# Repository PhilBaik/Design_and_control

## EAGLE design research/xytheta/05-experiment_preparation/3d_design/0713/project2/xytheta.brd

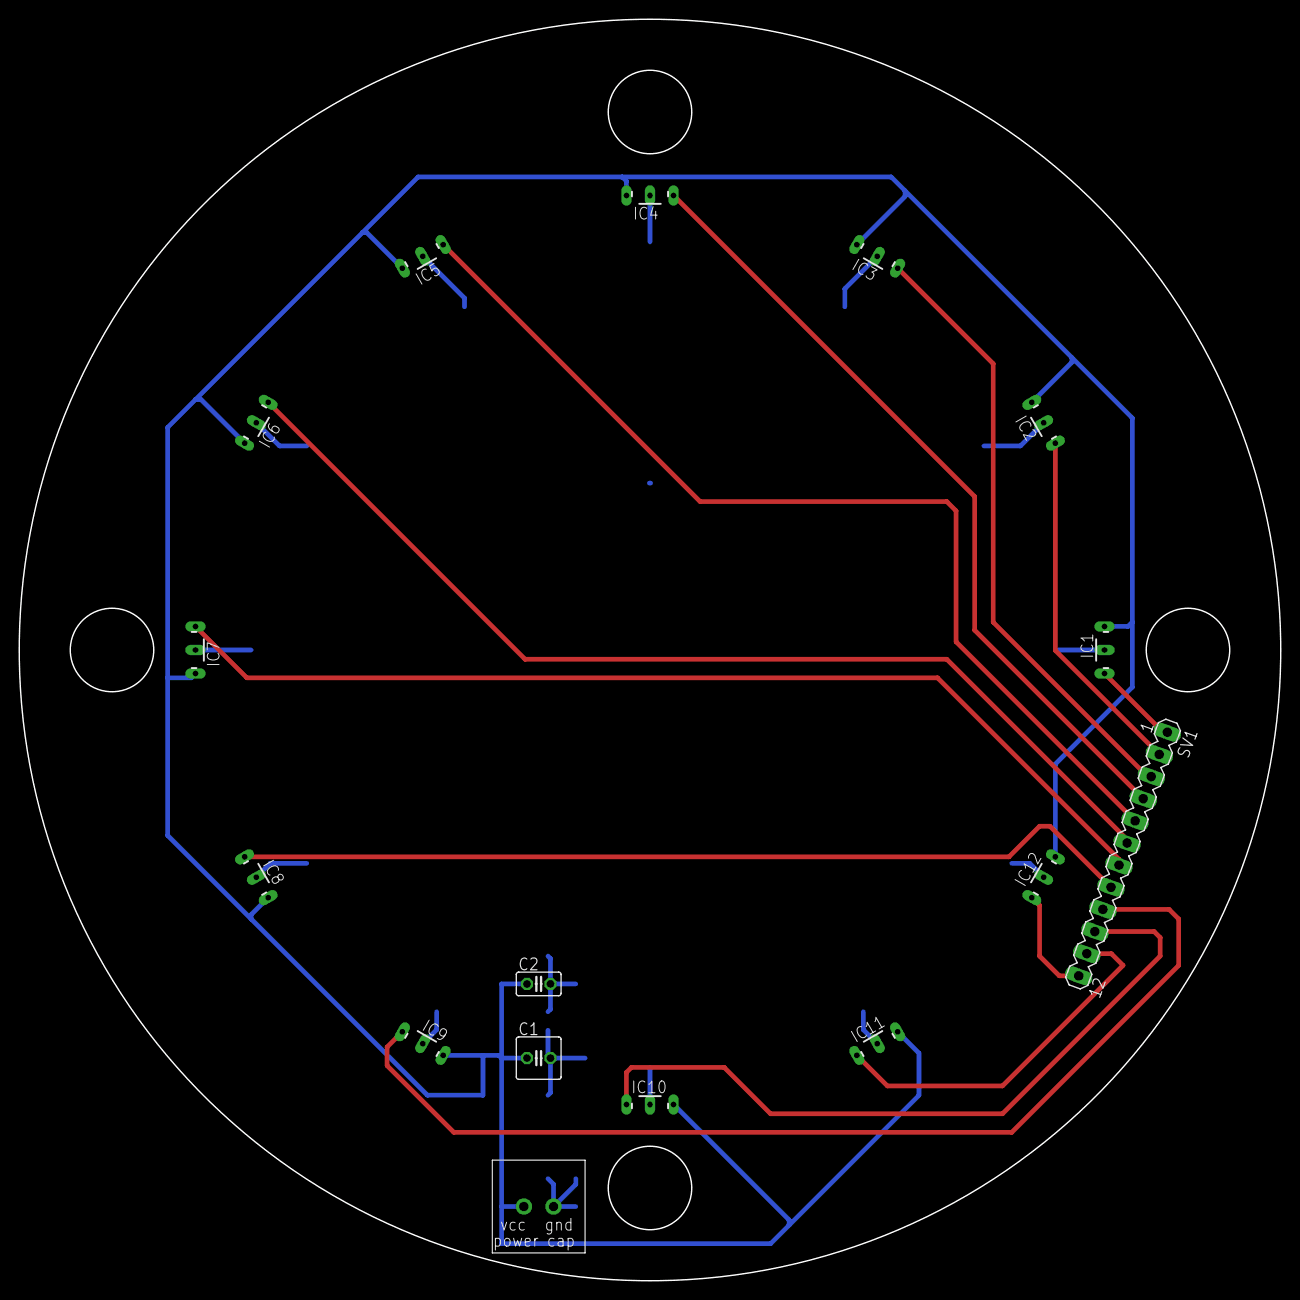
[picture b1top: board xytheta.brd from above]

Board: 2 copper layers, 136.0 x 136.0 mm, 16 parts (0 on the bottom side), 14 nets.

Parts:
C1: C025-050X050
C2: C025-025X050
IC1, IC2, IC3, IC4, IC5, IC6, IC7, IC8, IC9, IC10, IC11, IC12: A1302UA; SIP3-UA
SV1: MA12-1
U$1: POWERCAP

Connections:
unnamed: IC1.3, SV1.1
unnamed: IC2.3, SV1.2
unnamed: IC3.3, SV1.3
unnamed: IC4.3, SV1.4
unnamed: IC5.3, SV1.5
unnamed: IC6.3, SV1.6
unnamed: IC7.3, SV1.7
unnamed: IC8.3, SV1.8
unnamed: IC9.3, SV1.9
unnamed: IC10.3, SV1.10
unnamed: IC11.3, SV1.11
unnamed: IC12.3, SV1.12
unnamed: C1.1, C2.1, IC1.1, IC2.1, IC3.1, IC4.1, IC5.1, IC6.1, IC7.1, IC8.1, IC9.1, IC10.1, IC11.1, IC12.1, U$1.P$2
unnamed: C1.2, C2.2, IC1.2, IC2.2, IC3.2, IC4.2, IC5.2, IC6.2, IC7.2, IC8.2, IC9.2, IC10.2, IC11.2, IC12.2, U$1.P$1

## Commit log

2022-05-17 say hi
2022-05-18 feat: 기본적인 파일들 추가
2022-05-18 feat: LUT, microcontroller로 구성된 simulink 파일
2022-05-19 feat: dc motor, lpf hpf structure upload
2022-05-19 chore: folder checking
2022-05-19 Delete 무제.rtf
    chore: dump
2022-05-22 feat: propel1 stl, gcode
    propeller 파일
2022-05-22 feat: xytheta_plotting 함수 및 결과
2022-05-25 chore: renewing files
2022-05-25 feat: renewing files, LUT simulink
    folder hierarchy 최신화, 각 plot 추가, LUT simulink 자동화
2022-05-25 chore: deleting cash
2022-05-25 feat: new LUT output
    sensor_r 43, theta increment 5, kg3000
    from femm_out_sensor48_x[0,1]_y[2,10]
2022-05-25 feat: new femm output
    details are in mat.file
2022-05-25 chore: kg 10100 into 3000 for r48
2022-05-25 FIX: LUT is not compatible with monotonic decreasing y_position
2022-05-25 chore: deleting cache
2022-05-27 chore: correcting name
2022-05-27 chore:femm output renaming
2022-05-27 feat: mcu_plot revised 0526
    recommend to use m.file since .mlx does not support git
2022-05-27 feat: git attributes
2022-05-27 feat: flux checking without using LUT
2022-05-27 etc: just cache
2022-05-29 feat: automatically updating kg value
2022-05-29 docs: name substitution
2022-05-29 chore: getting new output for r43, r48
    r space = 15, 20
    x position -14 to 14, -18 to 18
2022-05-29 feat: new femm evaluation with efficient approach
2022-05-29 docs: renaming femm -> femm_naive
2022-05-30 chore: deleting irrelevant cache
2022-05-30 docs: hall sensor spec
2022-05-30 docs: xytheta paper 0530
2022-05-31 feat: plotting m file for paper
2022-05-31 fix: Babs can not be used
2022-05-31 docs: octavefemm manual
2022-05-31 fix: Babs should be orthogonal to the hall sensor
2022-05-31 TEST: sensor_r 48
2022-05-31 fix: femm setup change, r53 output
2022-06-23 feat: plotting for paper
    r = 53mm
2022-06-24 feat: efficient bug 수정 및 출력 output
2022-06-29 feat: 3d design xytheta stl files
2022-06-29 feat: 3d design of xytheta model, fusion 360 files
2022-07-03 feat: 0629 plot
2022-07-12 feat: to do list(hall sensor based sensor system 2)
2022-07-12 feat: eagle 0712
2022-07-12 chore: delete word
2022-07-13 feat: pcb
2022-07-19 chore: until 0719
2022-07-27 feat: LTSPICE models
2022-07-27 feat: 3d design of xy theta spacing 15, 20
    spacing 15 needed to be changed
2022-07-27 docs: revision of paper
    PWM-CFS
2022-07-27 chore: voltage_regulator.lib revision
2022-07-28 feat: LTSPICE manual 1 introduction
2022-07-28 feat: xytheta zig placement figure
    spacing 15
2022-08-03 chore: folder cleaning
2022-08-03 feat: xytheta_1_femm_efficient
2022-08-03 feat: femm_output r48 air , femm_efficient.m
2022-08-03 chore: deleting and relocating original files
2022-08-03 feat: enhancing efficiency of original code
2022-08-03 chore: relocating and deleting orignal files
2022-08-03 feat: new output
    femm r43, r48 air case
2022-08-03 feat: tiff files for r48 air case
2022-08-03 chore: changing folder hierarchy
2022-08-03 chore: folder hierarchy
2022-08-13 feat: magnetic_resolver checking codes, generating figures
2022-08-13 chore: trash
2022-08-15 docs: About RM57Lx
2022-08-15 feat: value checking magnetic resolver
2022-08-15 chore: figure hierarchy
2022-08-16 feat: adding 'addaxis6'
2022-08-16 feat: value check
    magnetic resolver
2022-08-16 chore: folder hierarchy and deleting trashes
2022-08-16 feat: revising Magnetic Resolver
2022-08-17 docs: arduino esc subscript
2022-08-17 feat: magnetic resolver plot
2022-08-17 feat: xytheta 3d design
2022-08-17 feat: magnetic resolver files
2022-08-23 docs: magnetic resolver revision 0823
2022-08-23 feat: 3d design changes
2022-08-28 feat: new 3d design
2022-08-31 chore: 0831
2022-10-02 feat: magnetic resolver v2. prof daniel
2022-10-03 feat: xytheta revision
2022-10-07 feat: xytheta data
2022-10-07 feat: xytheta data 2
2022-10-17 chore: extra xytheta
